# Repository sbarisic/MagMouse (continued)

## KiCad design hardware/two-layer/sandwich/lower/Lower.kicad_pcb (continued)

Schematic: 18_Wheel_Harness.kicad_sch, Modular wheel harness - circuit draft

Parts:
J8: Wheel 17-wire signals / 2 GND; Wire_Wheel_17_P2.54mm
R141, R142, R143: 33k; R_1206_3216Metric; Rating 0.25 W, 1%; MPN RC1206FR-0733KL

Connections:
+3V3: J8.16; also elsewhere on the board
ACT_DRIVE_EN: J8.13; also elsewhere on the board
ADC2_MISO_LOCAL: J8.9, R143.1; also elsewhere on the board
CS_ADC2: J8.8; also elsewhere on the board
CS_DRV8316: J8.4; also elsewhere on the board
DRV_FAULT_LOCAL_N: J8.15, R141.1; also elsewhere on the board
DRV_MISO_LOCAL: J8.5, R142.1; also elsewhere on the board
GND: J8.1, J8.17, R141.2, R142.2, R143.2; also elsewhere on the board
MOTOR_SPI_MOSI: J8.7; also elsewhere on the board
MOTOR_SPI_SCLK: J8.6; also elsewhere on the board
SPI_MOSI: J8.3; also elsewhere on the board
SPI_SCLK: J8.2; also elsewhere on the board
WHEEL_PWM_A: J8.10; also elsewhere on the board
WHEEL_PWM_B: J8.11; also elsewhere on the board
WHEEL_PWM_C: J8.12; also elsewhere on the board
WHEEL_RUN_REQ: J8.14; also elsewhere on the board

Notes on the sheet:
18_Wheel_Harness / Lower components See 20_Stack_Harness for the inter-board wiring.

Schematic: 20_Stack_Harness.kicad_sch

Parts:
H101, H102, H103, H104: M2 clearance / 5mm support envelope; MountingHole_2.2mm_M2_5mm_Envelope
J101: Stack signals / 14 wires; Wire_Stack_Signal_14
J103: Stack power / 5 wires; Wire_Stack_Power_5

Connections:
+3V3: J103.4; also elsewhere on the board
ACT_DRIVE_EN: J101.13; also elsewhere on the board
ACT_HEARTBEAT: J101.7; also elsewhere on the board
ACT_REQ: J101.6; also elsewhere on the board
ADC_CS: J101.5; also elsewhere on the board
CC_OUT1: J101.9; also elsewhere on the board
CC_OUT2: J101.10; also elsewhere on the board
GND: J101.1, J103.1, J103.5; also elsewhere on the board
HALL_EN: J101.12; also elsewhere on the board
MCU_EN: J101.14; also elsewhere on the board
PWR_5V: J103.3; also elsewhere on the board
SENS_REQ: J101.8; also elsewhere on the board
SPI_MISO: J101.4; also elsewhere on the board
SPI_MOSI: J101.3; also elsewhere on the board
SPI_SCLK: J101.2; also elsewhere on the board
VBUS_PRESENT_N: J101.11; also elsewhere on the board
VBUS_USB: J103.2; also elsewhere on the board

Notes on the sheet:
Connect equal-numbered signal and power pads between Lower and Upper. 19 wires total: 13 signals, 3 supply rails, 3 shared grounds. All three buttons use passive plastic clicks and Hall sensing.

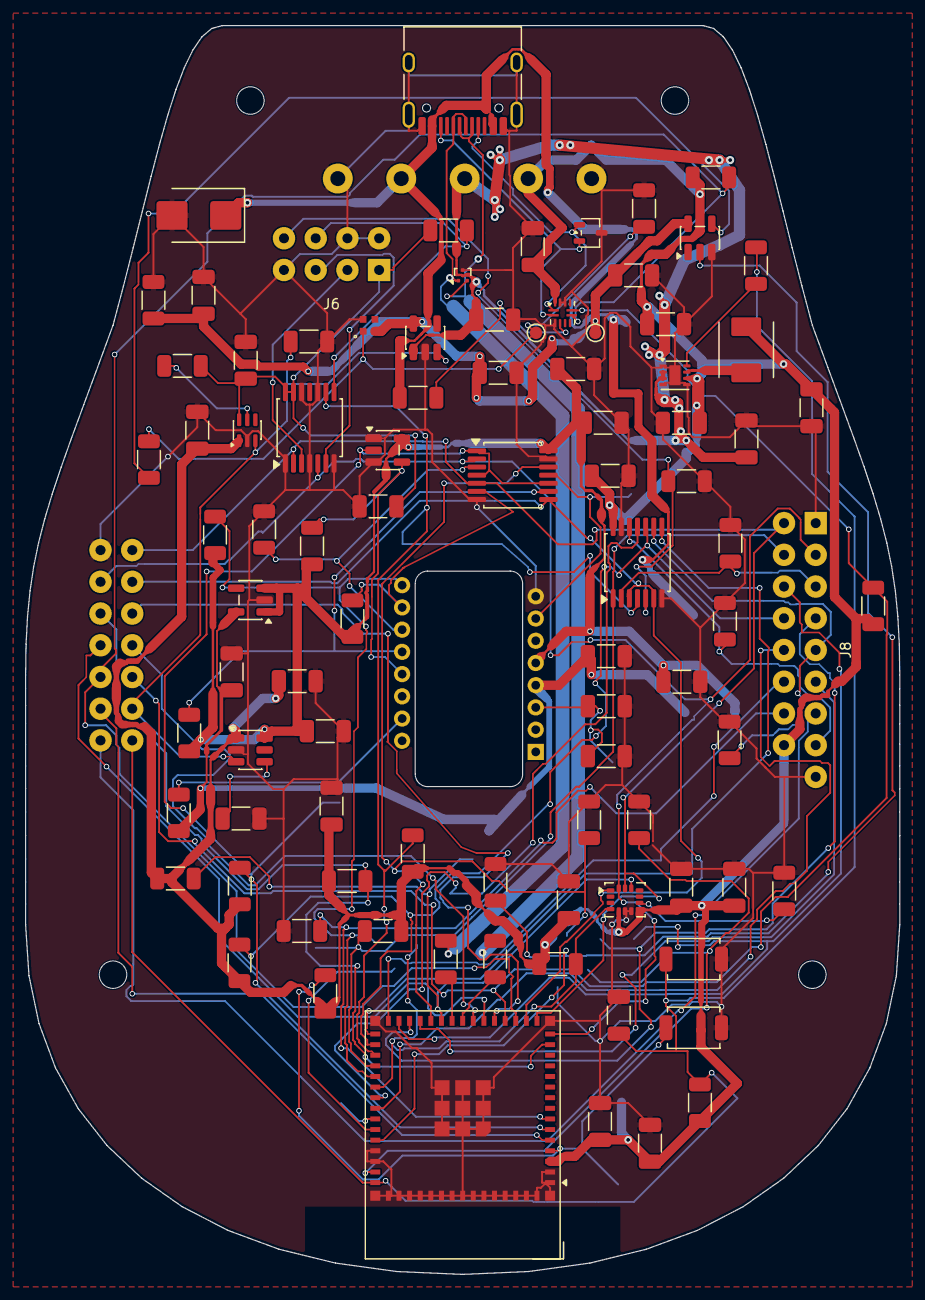
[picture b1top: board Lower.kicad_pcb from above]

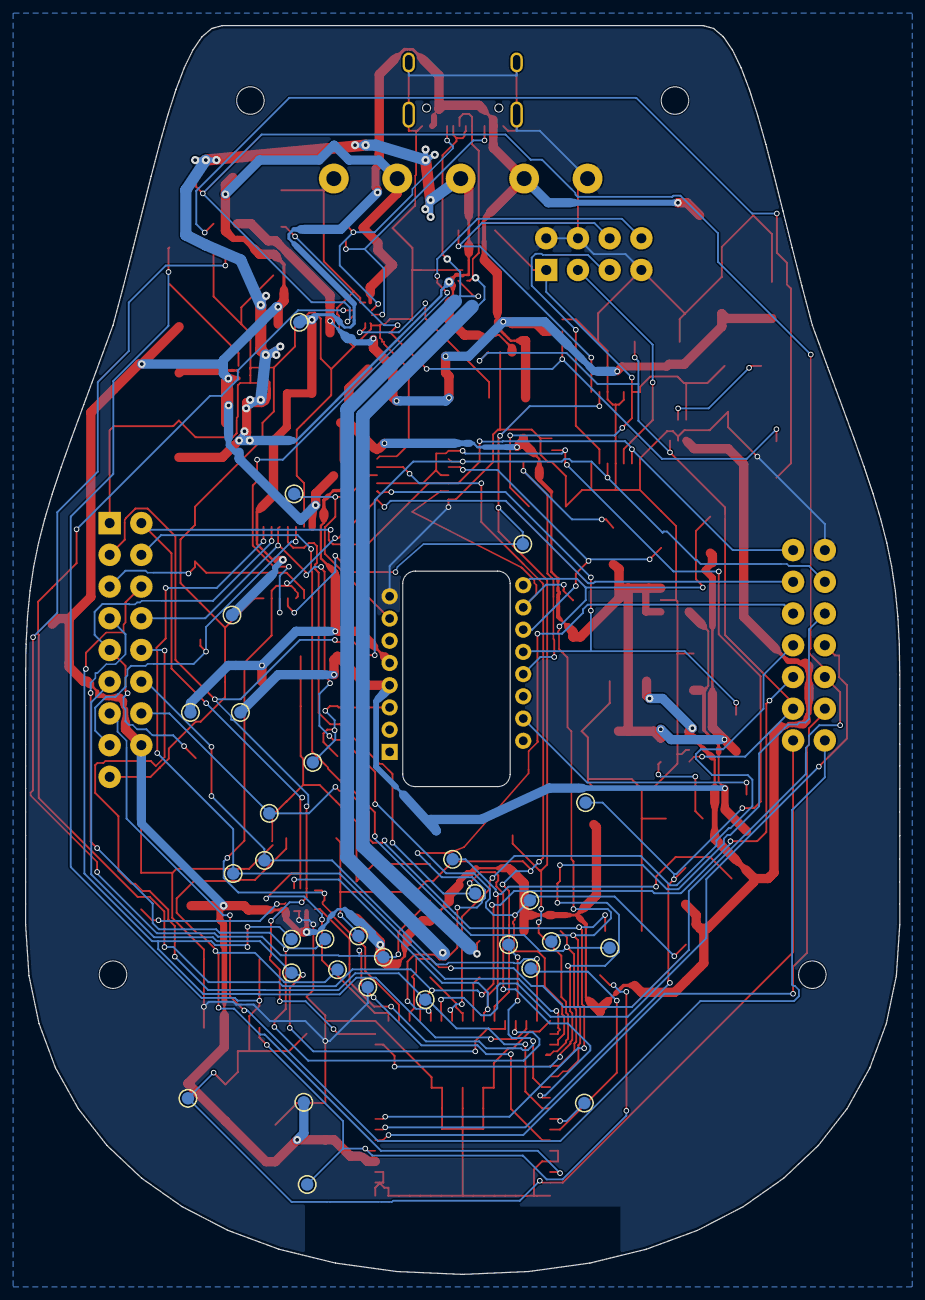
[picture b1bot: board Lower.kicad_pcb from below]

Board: 2 copper layers, 70.0 x 100.0 mm, 128 parts (30 on the bottom side), 70 nets.

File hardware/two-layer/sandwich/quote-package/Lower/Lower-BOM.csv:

Comment,Designator,Footprint,LCSC Part #,Manufacturer,MPN,Quantity
10uF/25V,"C1,C2,C23,C3,C5,C73,C74,C77,C78",C_1206_3216Metric,,Samsung Electro-Mechanics,CL31A106KAHNNNE,9
100nF,"C22,C53,C55,C6,C64,C70,C75,C76,C80,C83,C85,C86,C87",C_1206_3216Metric,,YAGEO,CC1206KRX7R9BB104,13
1uF/50V,"C4,C63",C_1206_3216Metric,,Samsung Electro-Mechanics,CL31B105KBHNNNE,2
2.2uF/10V,"C71,C81,C82",C_1206_3216Metric,,Samsung Electro-Mechanics,CL31B225KAHNNNE,3
10nF,C72,C_1206_3216Metric_OneSideSilk,,YAGEO,CC1206KRX7R9BB103,1
1nF/50V,C79,C_1206_3216Metric,,YAGEO,CC1206KRX7R9BB102,1
4.7uF/10V,C84,C_1206_3216Metric,,Samsung Electro-Mechanics,CL31A475KAHNNNE,1
SMBJ12A,D1,D_SMB,C151251,Littelfuse,SMBJ12A,1
SK6805-EC15,D5,OPSCO_SK6805_EC15,C2890035,OPSCO Optoelectronics,SK6805-EC15,1
TYPE-C-31-M-12,J1,USB_C_Receptacle_HRO_TYPE-C-31-M-12,C165948,Korean Hroparts Elec,TYPE-C-31-M-12,1
SRP4020CC-3R3M,L1,L_Bourns_SRP4020CC,,Bourns,SRP4020CC-3R3M,1
100k,"R101,R110,R129,R133,R134,R136,R26,R27",R_1206_3216Metric,,YAGEO,RC1206FR-07100KL,8
0R,R125,R_1206_3216Metric,,YAGEO,RC1206JR-070RL,1
10k,"R126,R127,R130,R131,R135,R3,R4,R7,R72,R73,R74,R75,R76,R77,R78,R79,R80,R99",R_1206_3216Metric,,YAGEO,RC1206FR-0710KL,18
330R,R128,R_1206_3216Metric,,YAGEO,RC1206FR-07330RL,1
39R,R132,R_1206_3216Metric,,YAGEO,RC1206FR-0739RL,1
33k,"R141,R142,R143",R_1206_3216Metric,,YAGEO,RC1206FR-0733KL,3
887k,R25,R_1206_3216Metric,,YAGEO,RC1206FR-07887KL,1
1k,R28,R_1206_3216Metric,,YAGEO,RC1206FR-071KL,1
33R,"R5,R6",R_1206_3216Metric,,YAGEO,RC1206FR-0733RL,2
RESET,SW1,SW_SPST_TS-1088-xR020,C720477,XUNPU,TS-1088-AR02016,1
BOOT,SW2,SW_SPST_TS-1088-xR020,C720477,XUNPU,TS-1088-AR02016,1
TPD2EUSB30DRTR,U1,Texas_DRT-3,C97502,Texas Instruments,TPD2EUSB30DRTR,1
TUSB320LAIRWBR,U11,Texas_X2QFN-12_1.6x1.6mm_P0.4mm,C132554,Texas Instruments,TUSB320LAIRWBR,1
TPS62162DSGR,U2,Texas_DSG0008A_WSON-8-1EP_2x2mm_P0.5mm_EP0.9x1.6mm,C40256,Texas Instruments,TPS62162DSGR,1
TPD2E2U06DCKR,U20,SOT-323_SC-70,C1855726,Texas Instruments,TPD2E2U06DCKR,1
SN74LVC125APWR,"U25,U29,U37",TSSOP-14_4.4x5mm_P0.65mm,C7813,Texas Instruments,SN74LVC125APWR,3
TPS22919DCKR,U28,SOT-363_SC-70-6,C2149796,Texas Instruments,TPS22919DCKR,1
ESP32-S3-MINI-1-N8,U3,ESP32-S2-MINI-1,C2913206,Espressif Systems,ESP32-S3-MINI-1-N8,1
ICM-42688-P,U32,LGA-14_3x2.5mm_P0.5mm_LayoutBorder3x4y,C1850418,TDK InvenSense,ICM-42688-P,1
TPS7A2450DBVR,U33,SOT-23-5,C2864436,Texas Instruments,TPS7A2450DBVR,1
SN74LV1T34DBVR,U34,SOT-23-5,C100024,Texas Instruments,SN74LV1T34DBVR,1
PMW3360DM-T2QU,U35,PixArt_PMW3360DM_T2QU,C20612443,PixArt,PMW3360DM-T2QU,1
TLV75519PDBVR,U36,SOT-23-5,C2865381,Texas Instruments,TLV75519PDBVR,1
TPS22918DBVR,U38,SOT-23-6,C131941,Texas Instruments,TPS22918DBVR,1
SN74LVC1G125DBVR,U39,SOT-23-5,C23654,Texas Instruments,SN74LVC1G125DBVR,1

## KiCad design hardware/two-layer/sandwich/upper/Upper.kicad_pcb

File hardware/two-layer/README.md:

# Active two-layer PCBs

Open the [stacked-board project overview](sandwich/README.md).

| Board | Project | Outline |
|---|---|---|
| Lower Main | [Lower](sandwich/lower/Lower.kicad_pro) | 70 x 100 mm tapered |
| Upper Main | [Upper](sandwich/upper/Upper.kicad_pro) | 70 x 100 mm tapered |
| Wheel | [Wheel](sandwich/wheel/Wheel.kicad_pro) | 70 x 67 mm clipped Main profile |
| Encoder | [Encoder](encoder/Encoder.kicad_pro) | 14 x 18 mm with upper chamfers |

The `sandwich` directory contains the active routing tools, review evidence,
3D exports, current quote packages and four-board panel. `main-circuit` is the
combined schematic reference used to check the Lower/Upper partition; edit the
independent board schematics for development. Shared resources are in
[hardware/common](../common/README.md).

The oversized two-layer experiments and their one-time conversion scripts have
been removed from this checkout. They remain in [Git history](../../docs/history/README.md).

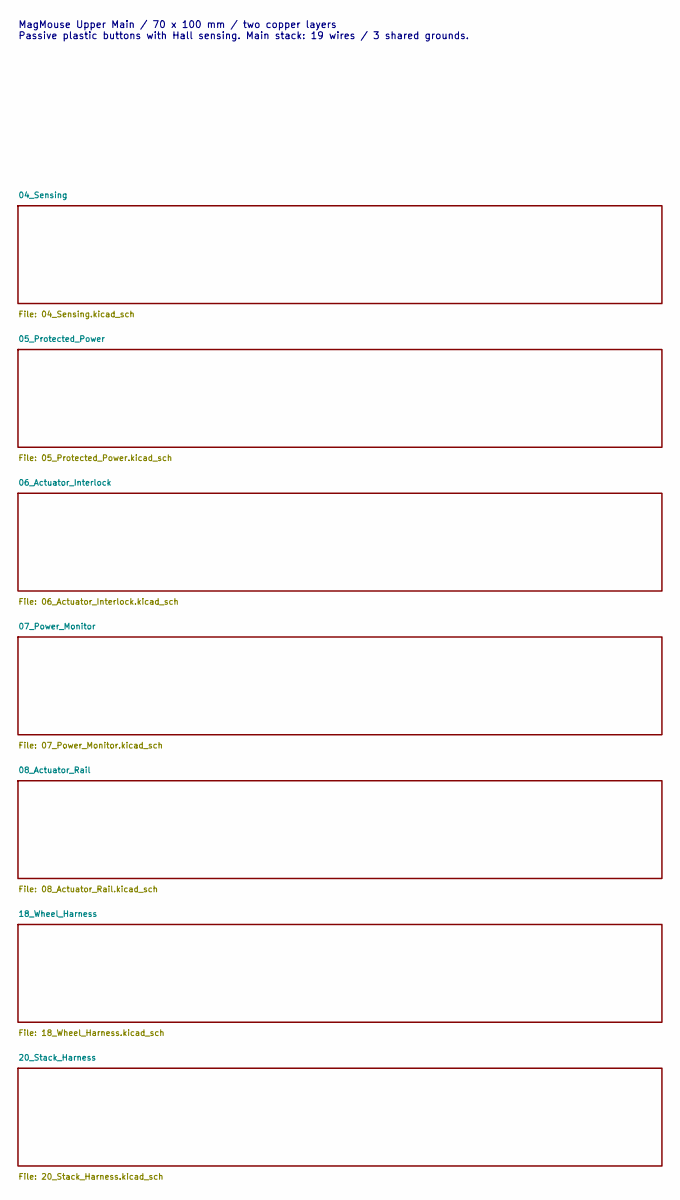
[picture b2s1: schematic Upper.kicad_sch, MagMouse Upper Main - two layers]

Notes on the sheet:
MagMouse Upper Main / 70 x 100 mm / two copper layers Passive plastic buttons with Hall sensing. Main stack: 19 wires / 3 shared grounds.

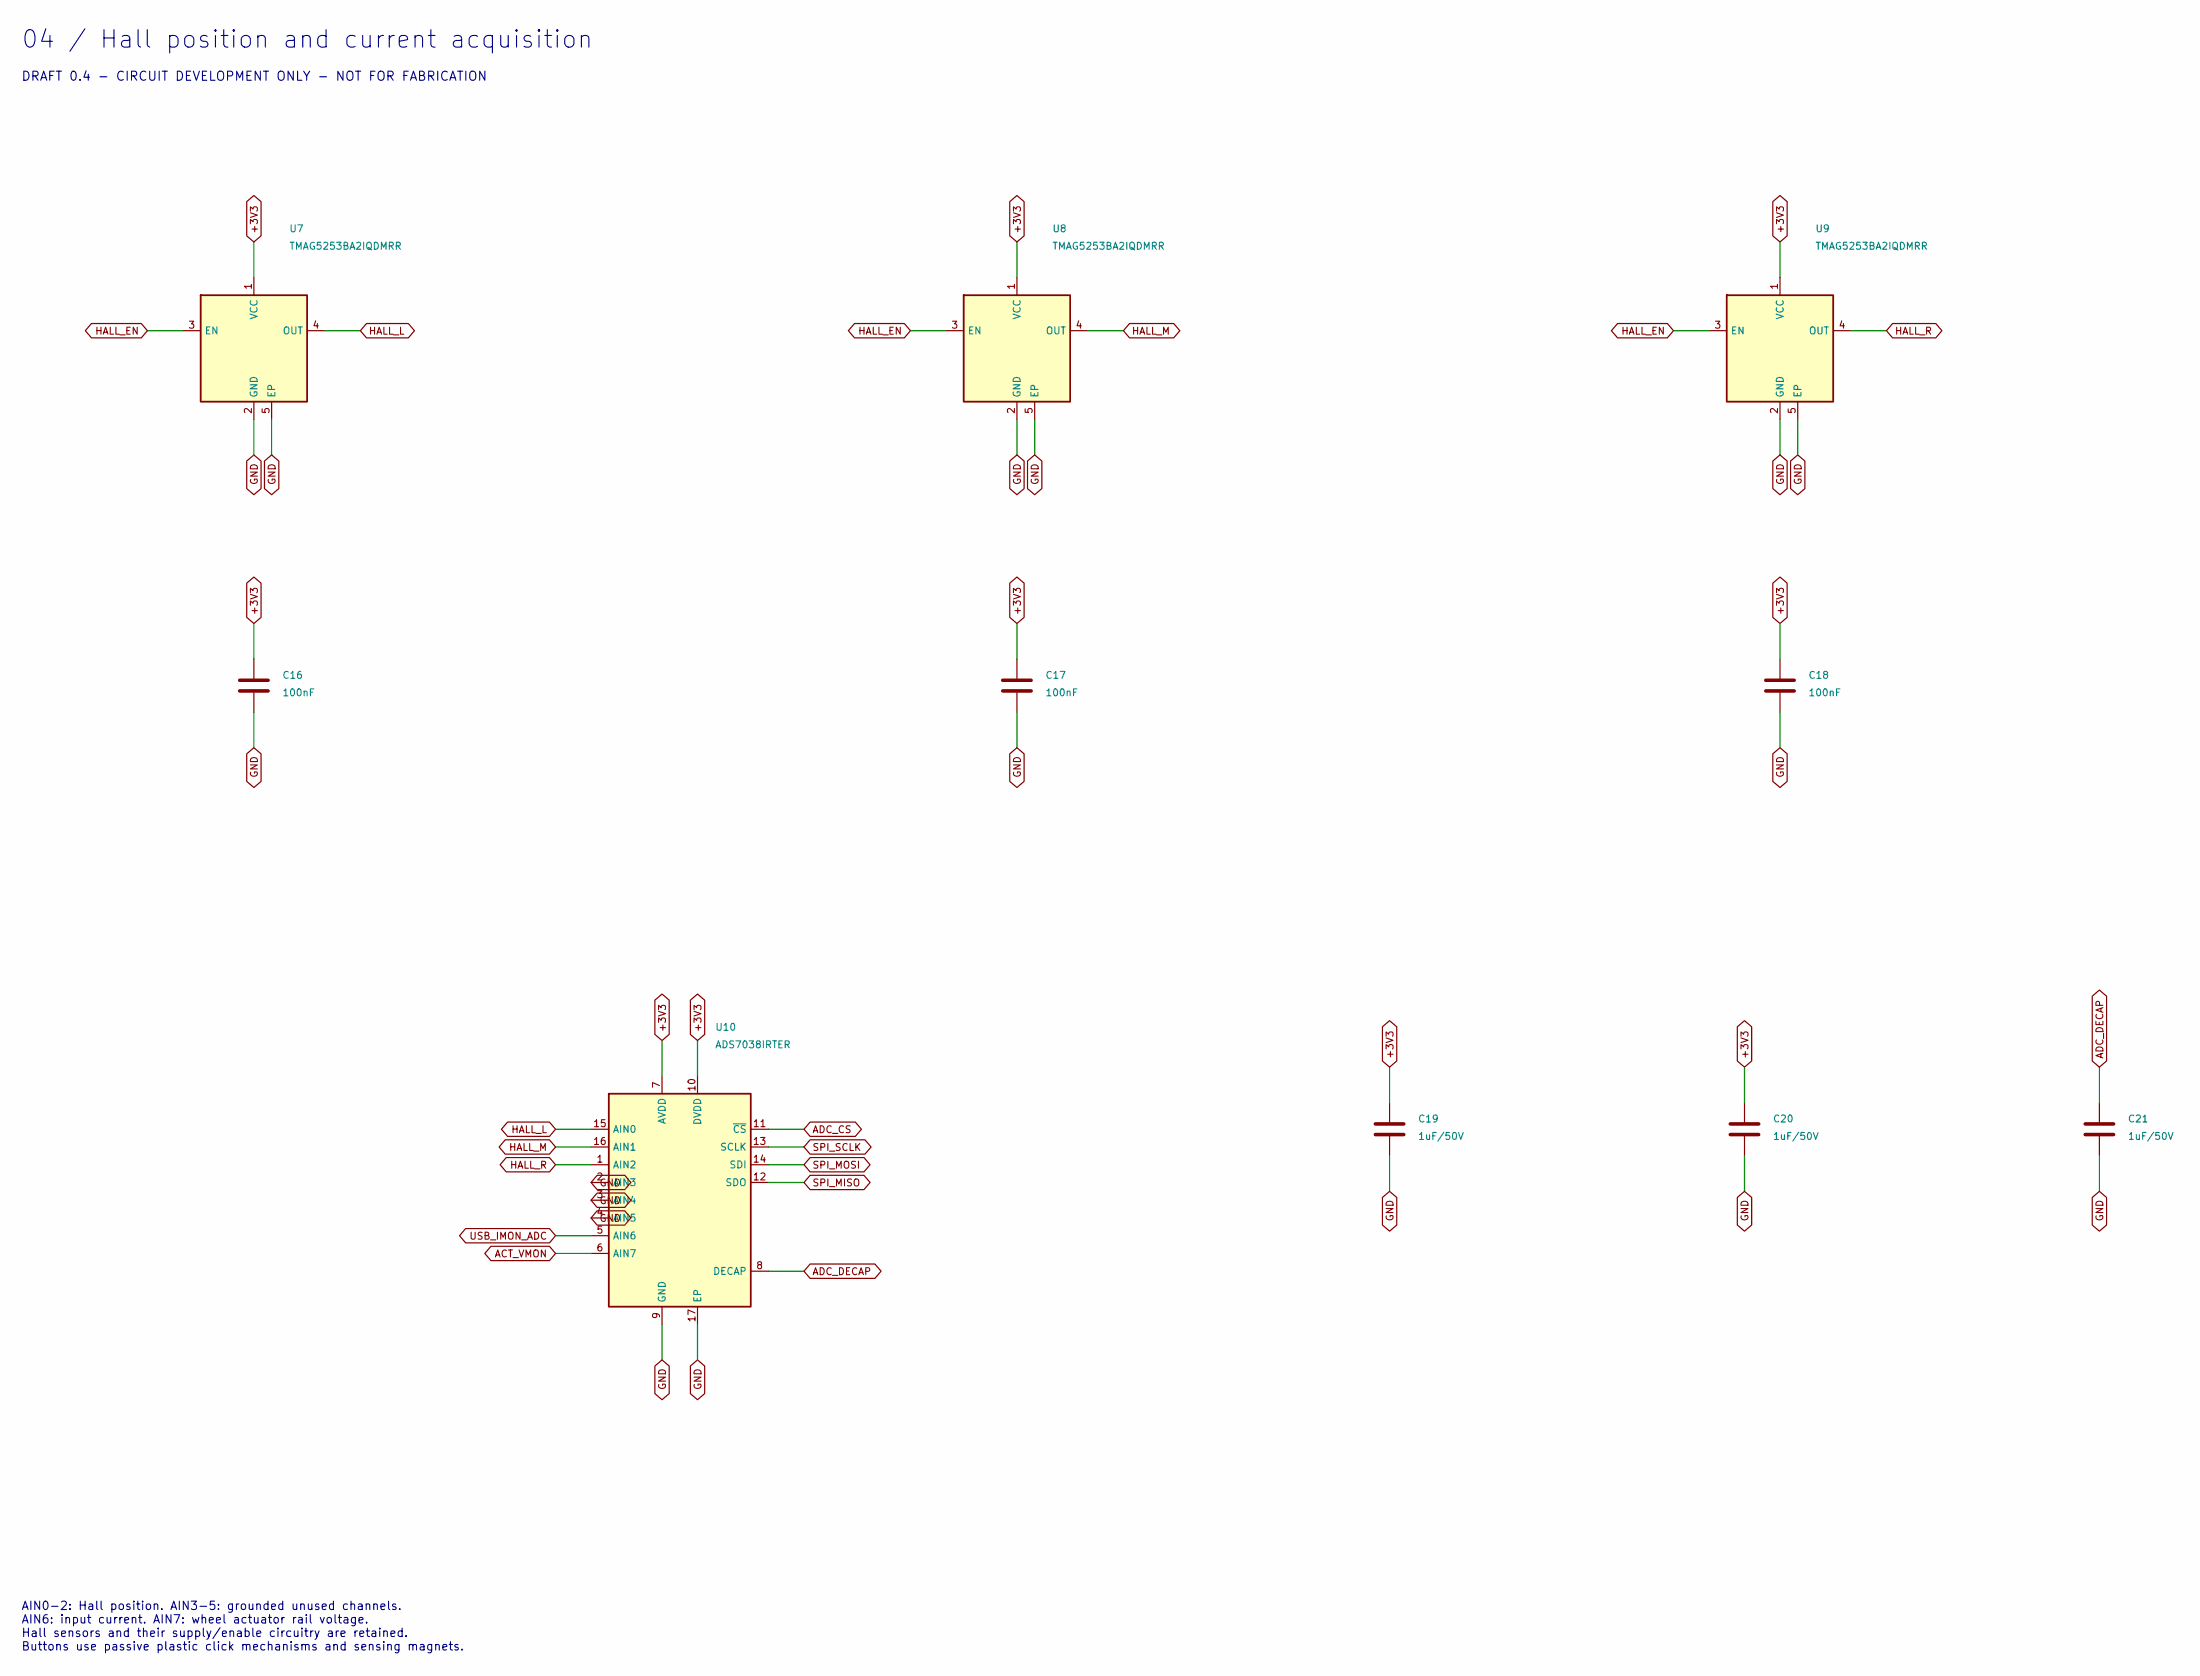
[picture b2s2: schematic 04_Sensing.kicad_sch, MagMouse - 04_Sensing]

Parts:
C16, C17, C18: 100nF; C_1206_3216Metric; Rating 50 V, X7R, 10%; MPN CC1206KRX7R9BB104
C19, C20, C21: 1uF/50V; C_1206_3216Metric; Rating 50 V, X7R, 10%; MPN CL31B105KBHNNNE; JLCPCB Library Type Basic
U7, U8, U9: TMAG5253BA2IQDMRR; Texas_X2SON-4-1EP_1.1x1.4mm_P0.5mm_EP0.8x0.6mm; MPN TMAG5253BA2IQDMRR; LCSC C35414983
U10: ADS7038IRTER; WQFN-16-1EP_3x3mm_P0.5mm_EP1.68x1.68mm; MPN ADS7038IRTER; LCSC C2871580

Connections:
+3V3: C16.1, C17.1, C18.1, C19.1, C20.1, U7.1 (VCC), U8.1 (VCC), U9.1 (VCC), U10.7 (AVDD), U10.10 (DVDD); also elsewhere on the board
ACT_VMON: U10.6 (AIN7); also elsewhere on the board
ADC_CS: U10.11 (~CS); also elsewhere on the board
ADC_DECAP: C21.1, U10.8 (DECAP)
GND: C16.2, C17.2, C18.2, C19.2, C20.2, C21.2, U7.2 (GND), U7.5 (EP), U8.2 (GND), U8.5 (EP), U9.2 (GND), U9.5 (EP), U10.2 (AIN3), U10.3 (AIN4), U10.4 (AIN5), U10.9 (GND), U10.17 (EP); also elsewhere on the board
HALL_EN: U7.3 (EN), U8.3 (EN), U9.3 (EN); also elsewhere on the board
HALL_L: U7.4 (OUT), U10.15 (AIN0)
HALL_M: U8.4 (OUT), U10.16 (AIN1)
HALL_R: U9.4 (OUT), U10.1 (AIN2)
SPI_MISO: U10.12 (SDO); also elsewhere on the board
SPI_MOSI: U10.14 (SDI); also elsewhere on the board
SPI_SCLK: U10.13 (SCLK); also elsewhere on the board
USB_IMON_ADC: U10.5 (AIN6); also elsewhere on the board

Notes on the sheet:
04 / Hall position and current acquisition
DRAFT 0.4 - CIRCUIT DEVELOPMENT ONLY - NOT FOR FABRICATION
AIN0-2: Hall position. AIN3-5: grounded unused channels. AIN6: input current. AIN7: wheel actuator rail voltage. Hall sensors and their supply/enable circuitry are retained. Buttons use passive plastic click mechanisms and sensing magnets.

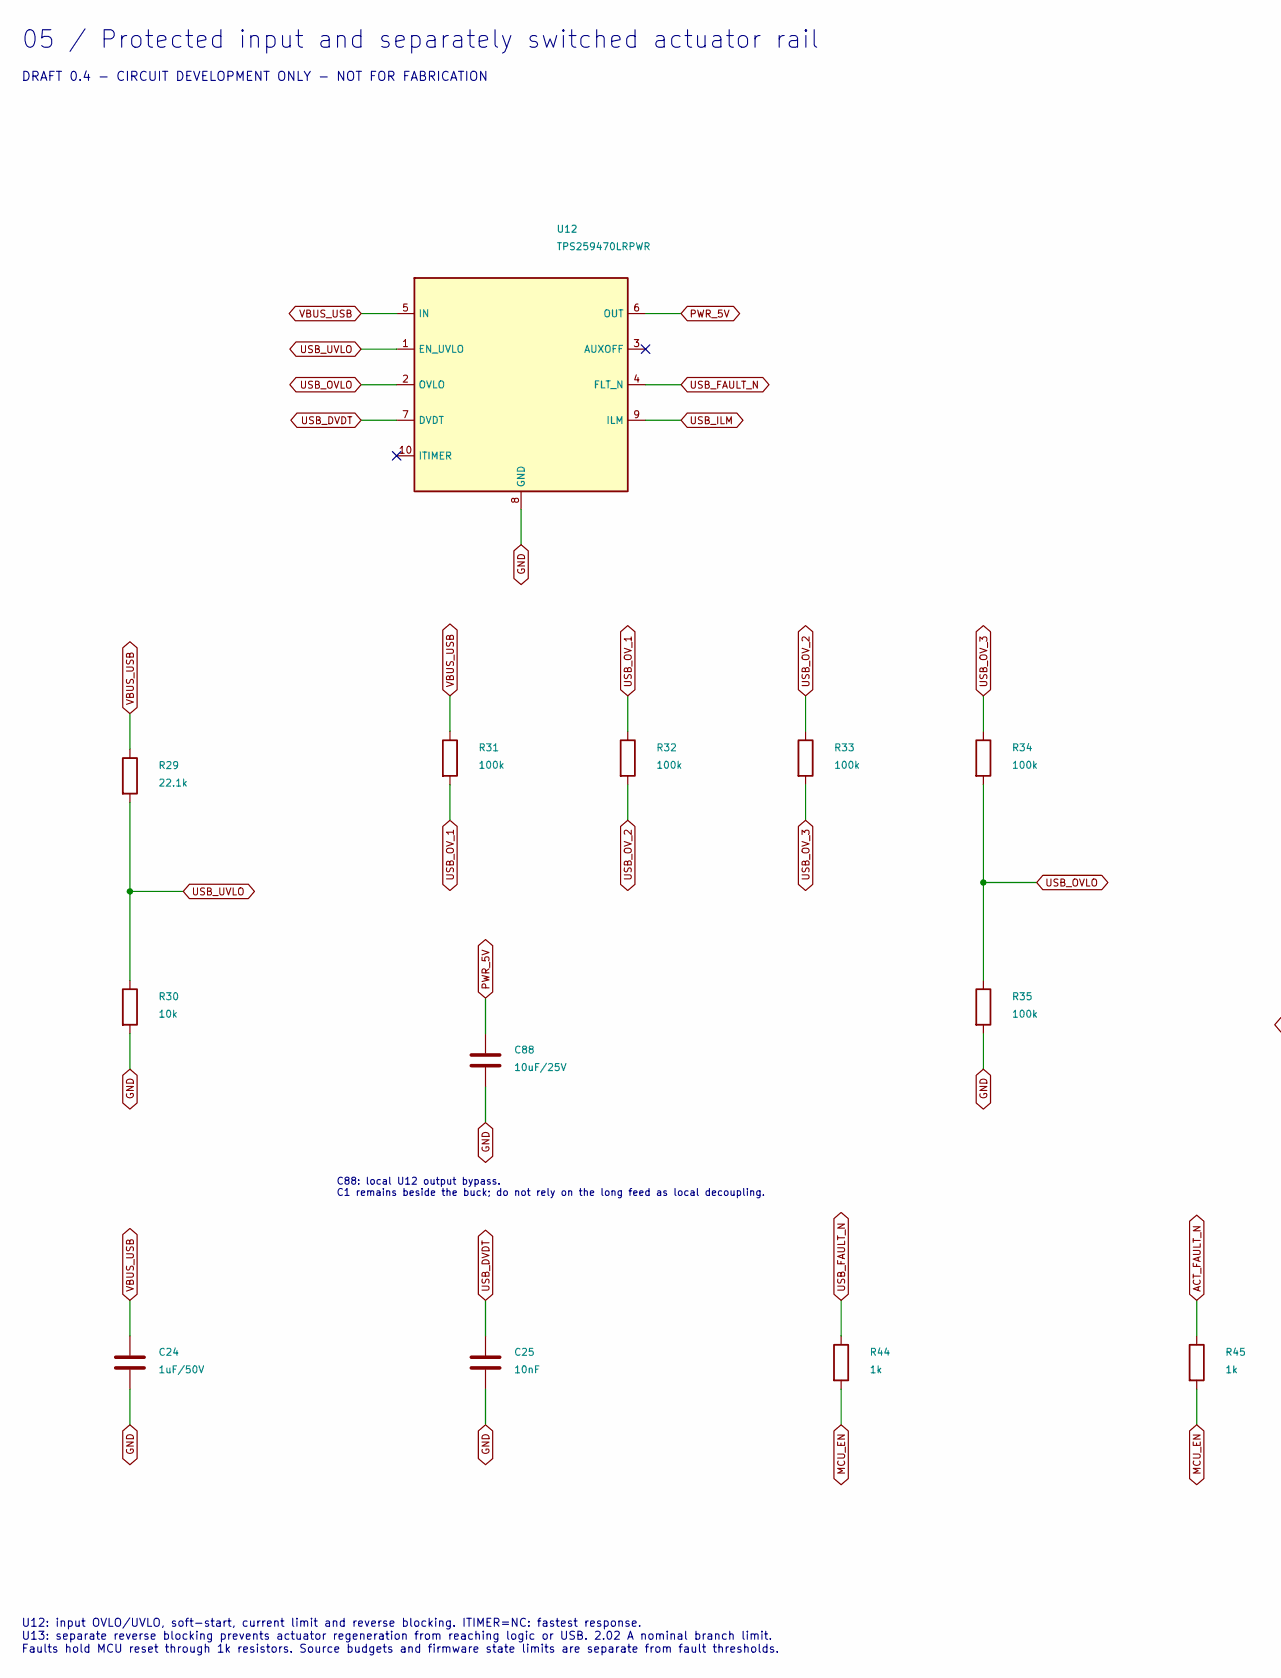
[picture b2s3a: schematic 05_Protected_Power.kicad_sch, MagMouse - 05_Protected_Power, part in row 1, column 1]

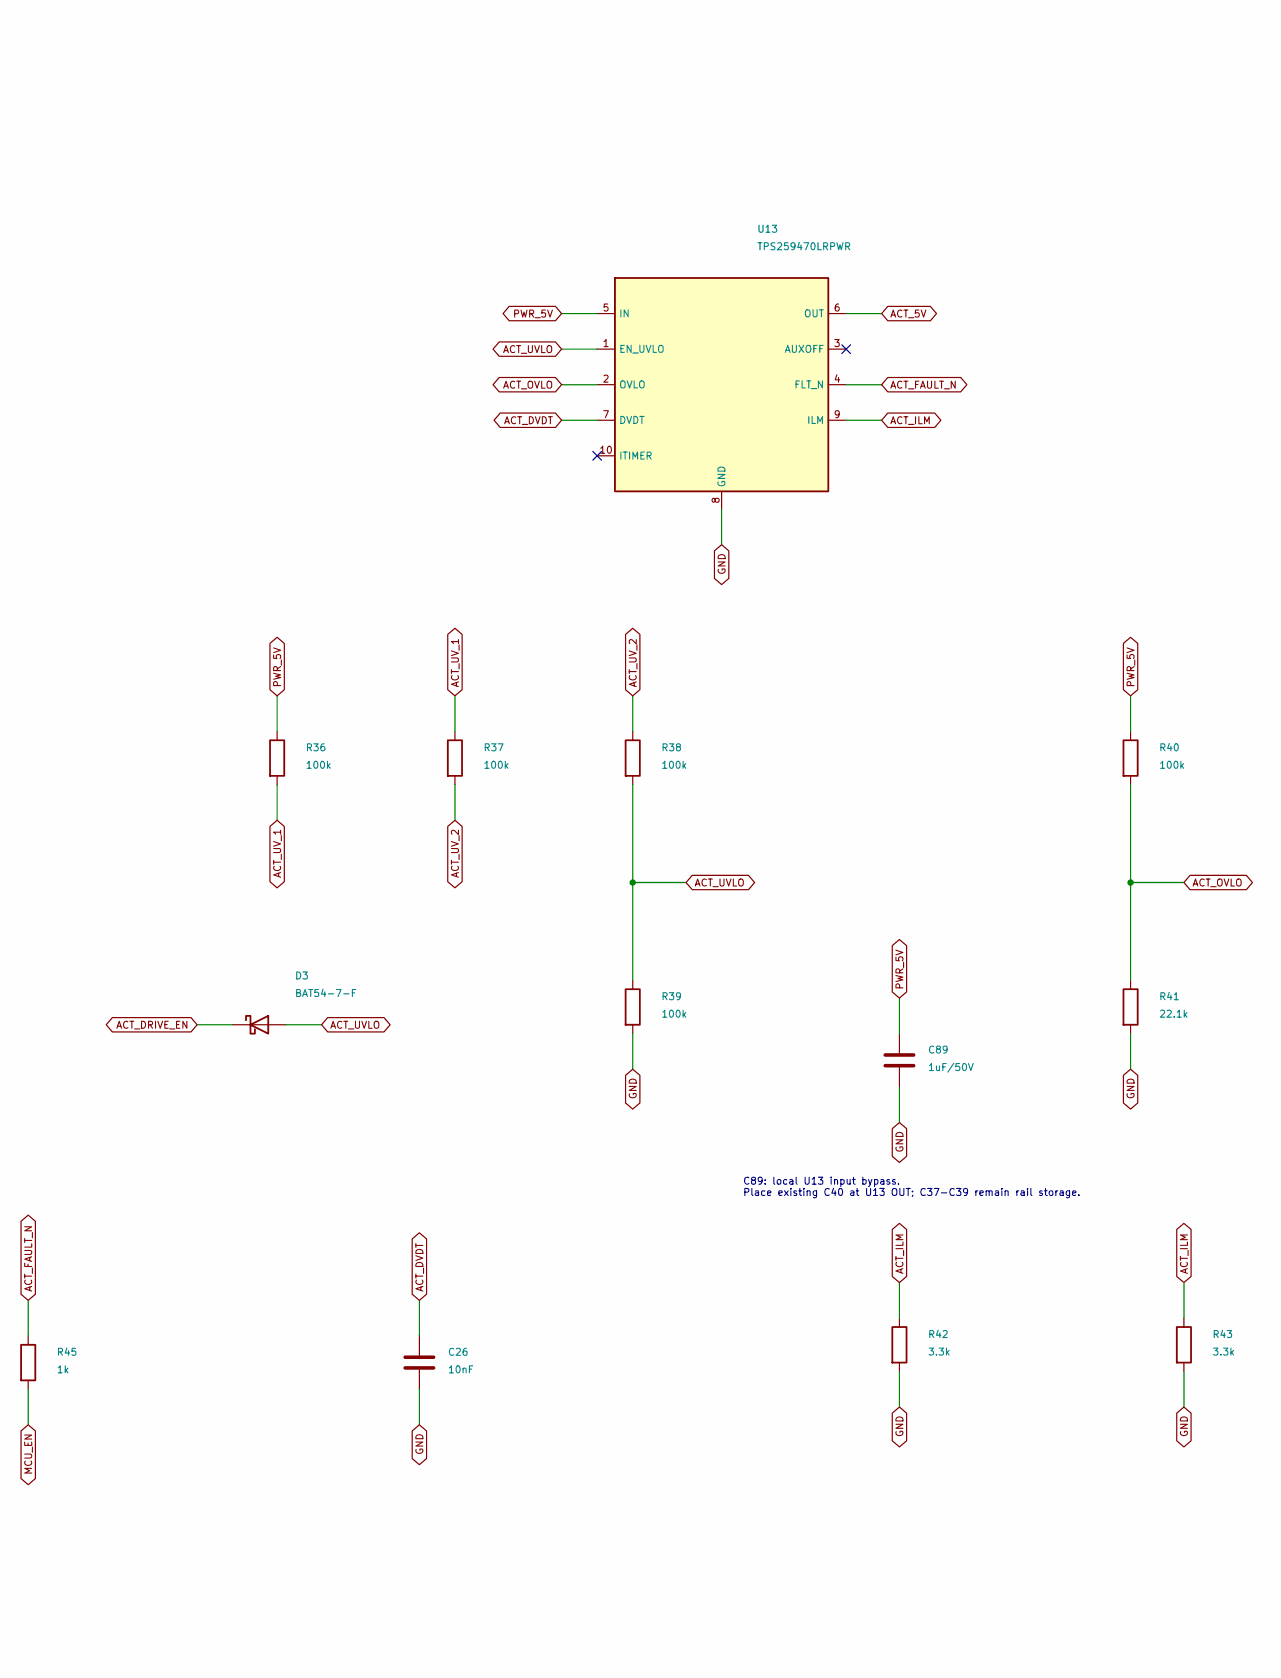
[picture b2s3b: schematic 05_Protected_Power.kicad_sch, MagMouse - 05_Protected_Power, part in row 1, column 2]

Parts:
C24, C89: 1uF/50V; C_1206_3216Metric; Rating 50 V, X7R, 10%; MPN CL31B105KBHNNNE
C25, C26: 10nF; C_1206_3216Metric; Rating 50 V, X7R, 10%; MPN CC1206KRX7R9BB103
C88: 10uF/25V; C_1206_3216Metric; Rating 25 V, X5R, 10%; MPN CL31A106KAHNNNE
D3: BAT54-7-F; SOT-23; MPN BAT54-7-F; LCSC C106920
R29, R41: 22.1k; R_1206_3216Metric; Rating 0.25 W, 1%; MPN RC1206FR-0722K1L
R30: 10k; R_1206_3216Metric; Rating 0.25 W, 1%; MPN RC1206FR-0710KL
R31, R32, R33, R34, R35, R36, R37, R38, R39, R40: 100k; R_1206_3216Metric; Rating 0.25 W, 1%; MPN RC1206FR-07100KL
R42, R43: 3.3k; R_1206_3216Metric; Rating 0.25 W, 1%; MPN RC1206FR-073K3L
R44, R45: 1k; R_1206_3216Metric; Rating 0.25 W, 1%; MPN RC1206FR-071KL
U12, U13: TPS259470LRPWR; Texas_RPW0010A; MPN TPS259470LRPWR; LCSC C3662793

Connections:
ACT_5V: U13.6 (OUT); also elsewhere on the board
ACT_DRIVE_EN: D3.3 (K); also elsewhere on the board
ACT_DVDT: C26.1, U13.7 (DVDT)
ACT_FAULT_N: R45.1, U13.4 (FLT_N)
ACT_ILM: R42.1, R43.1, U13.9 (ILM)
ACT_OVLO: R40.2, R41.1, U13.2 (OVLO)
ACT_UVLO: D3.1 (A), R38.2, R39.1, U13.1 (EN_UVLO)
ACT_UV_1: R36.2, R37.1
ACT_UV_2: R37.2, R38.1
GND: C24.2, C25.2, C26.2, C88.2, C89.2, R30.2, R35.2, R39.2, R41.2, R42.2, R43.2, U12.8 (GND), U13.8 (GND); also elsewhere on the board
MCU_EN: R44.2, R45.2; also elsewhere on the board
PWR_5V: C88.1, C89.1, R36.1, R40.1, U12.6 (OUT), U13.5 (IN); also elsewhere on the board
USB_DVDT: C25.1, U12.7 (DVDT)
USB_FAULT_N: R44.1, U12.4 (FLT_N)
USB_ILM: U12.9 (ILM); also elsewhere on the board
USB_OVLO: R34.2, R35.1, U12.2 (OVLO)
USB_OV_1: R31.2, R32.1
USB_OV_2: R32.2, R33.1
USB_OV_3: R33.2, R34.1
USB_UVLO: R29.2, R30.1, U12.1 (EN_UVLO)
VBUS_USB: C24.1, R29.1, R31.1, U12.5 (IN); also elsewhere on the board

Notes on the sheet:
05 / Protected input and separately switched actuator rail
DRAFT 0.4 - CIRCUIT DEVELOPMENT ONLY - NOT FOR FABRICATION
U12: input OVLO/UVLO, soft-start, current limit and reverse blocking. ITIMER=NC: fastest response. U13: separate reverse blocking prevents actuator regeneration from reaching logic or USB. 2.02 A nominal branch limit. Faults hold MCU reset through 1k resistors. Source budgets and firmware state lim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
C88: local U12 output bypass. C1 remains beside the buck; do not rely on the long feed as local decoupling.
C89: local U13 input bypass. Place existing C40 at U13 OUT; C37-C39 remain rail storage.

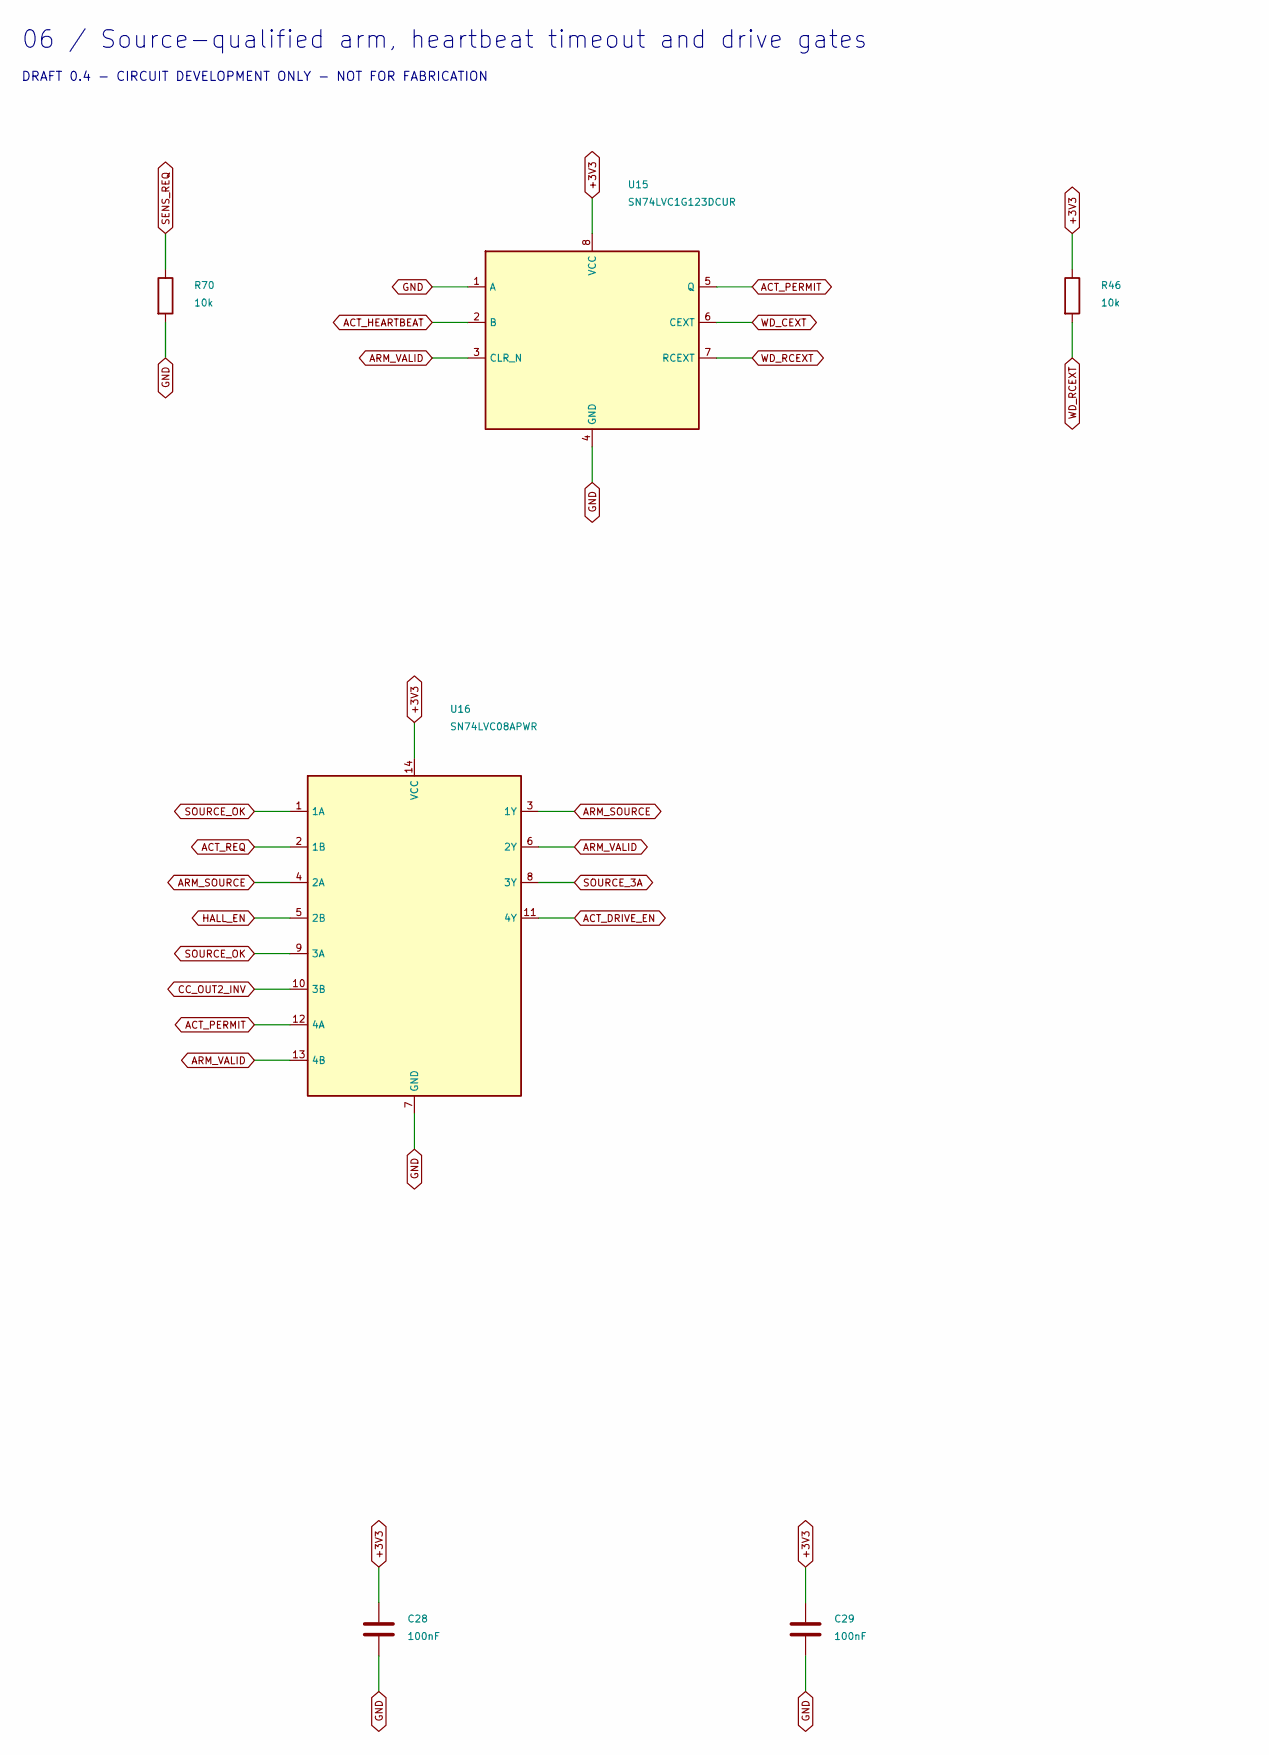
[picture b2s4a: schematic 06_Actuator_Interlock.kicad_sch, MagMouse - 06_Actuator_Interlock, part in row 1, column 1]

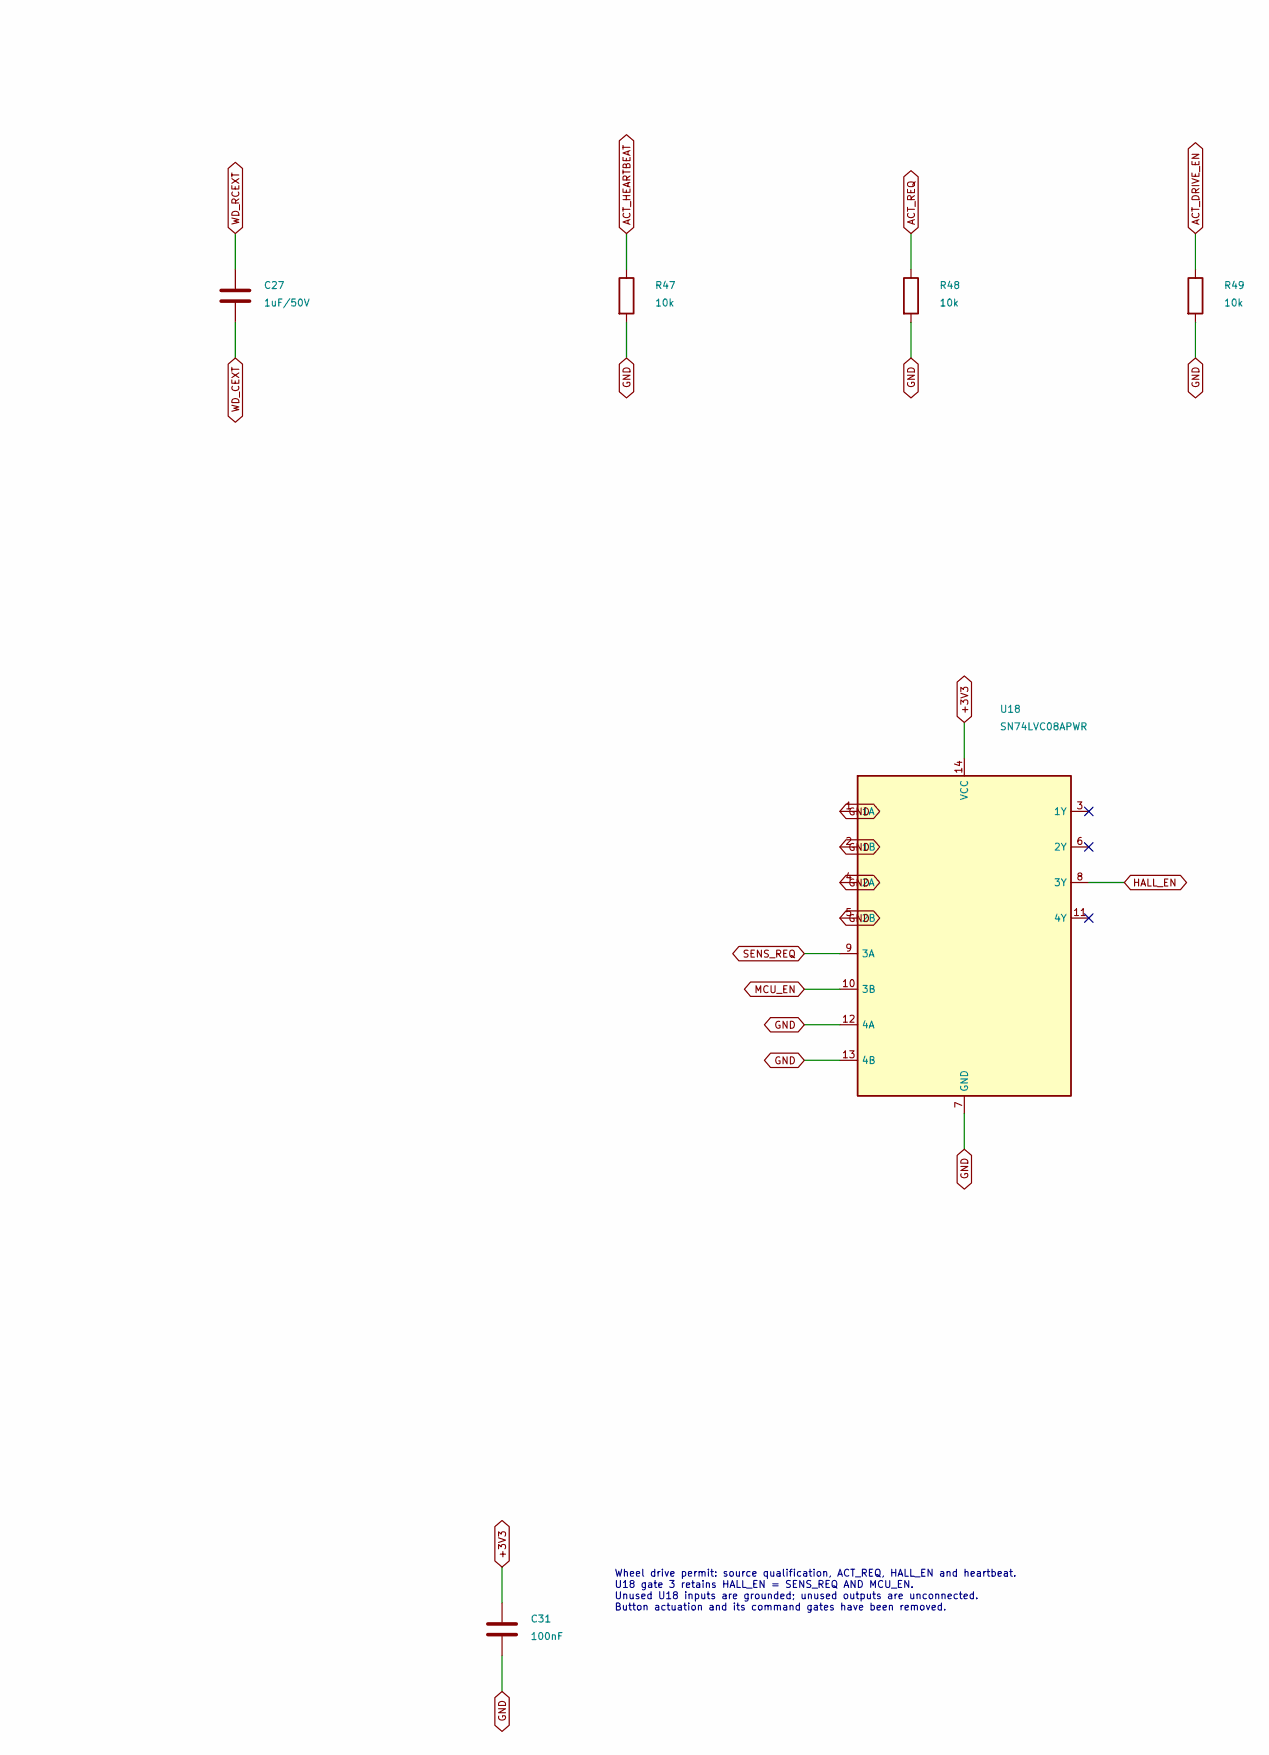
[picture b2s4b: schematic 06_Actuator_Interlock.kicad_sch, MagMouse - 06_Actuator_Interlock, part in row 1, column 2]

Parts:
C27: 1uF/50V; C_1206_3216Metric; Rating 50 V, X7R, 10%; MPN CL31B105KBHNNNE
C28, C29, C31: 100nF; C_1206_3216Metric; Rating 50 V, X7R, 10%; MPN CC1206KRX7R9BB104
R46, R47, R48, R49, R70: 10k; R_1206_3216Metric; Rating 0.25 W, 1%; MPN RC1206FR-0710KL
U15: SN74LVC1G123DCUR; VSSOP-8_2.3x2mm_P0.5mm; MPN SN74LVC1G123DCUR; LCSC C352969
U16, U18: SN74LVC08APWR; TSSOP-14_4.4x5mm_P0.65mm; MPN SN74LVC08APWR; LCSC C465737

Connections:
+3V3: C28.1, C29.1, C31.1, R46.1, U15.8 (VCC), U16.14 (VCC), U18.14 (VCC); also elsewhere on the board
ACT_DRIVE_EN: R49.1, U16.11 (4Y); also elsewhere on the board
ACT_HEARTBEAT: R47.1, U15.2 (B); also elsewhere on the board
ACT_PERMIT: U15.5 (Q), U16.12 (4A)
ACT_REQ: R48.1, U16.2 (1B); also elsewhere on the board
ARM_SOURCE: U16.3 (1Y), U16.4 (2A)
ARM_VALID: U15.3 (CLR_N), U16.6 (2Y), U16.13 (4B)
CC_OUT2_INV: U16.10 (3B); also elsewhere on the board
GND: C28.2, C29.2, C31.2, R47.2, R48.2, R49.2, R70.2, U15.1 (A), U15.4 (GND), U16.7 (GND), U18.1 (1A), U18.2 (1B), U18.4 (2A), U18.5 (2B), U18.7 (GND), U18.12 (4A), U18.13 (4B); also elsewhere on the board
HALL_EN: U16.5 (2B), U18.8 (3Y); also elsewhere on the board
MCU_EN: U18.10 (3B); also elsewhere on the board
SENS_REQ: R70.1, U18.9 (3A); also elsewhere on the board
SOURCE_3A: U16.8 (3Y); also elsewhere on the board
SOURCE_OK: U16.1 (1A), U16.9 (3A); also elsewhere on the board
WD_CEXT: C27.2, U15.6 (CEXT)
WD_RCEXT: C27.1, R46.2, U15.7 (RCEXT)

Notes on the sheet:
06 / Source-qualified arm, heartbeat timeout and drive gates
DRAFT 0.4 - CIRCUIT DEVELOPMENT ONLY - NOT FOR FABRICATION
Wheel drive permit: source qualification, ACT_REQ, HALL_EN and heartbeat. U18 gate 3 retains HALL_EN = SENS_REQ AND MCU_EN. Unused U18 inputs are grounded; unused outputs are unconnected. Button actuation and its command gates have been removed.
